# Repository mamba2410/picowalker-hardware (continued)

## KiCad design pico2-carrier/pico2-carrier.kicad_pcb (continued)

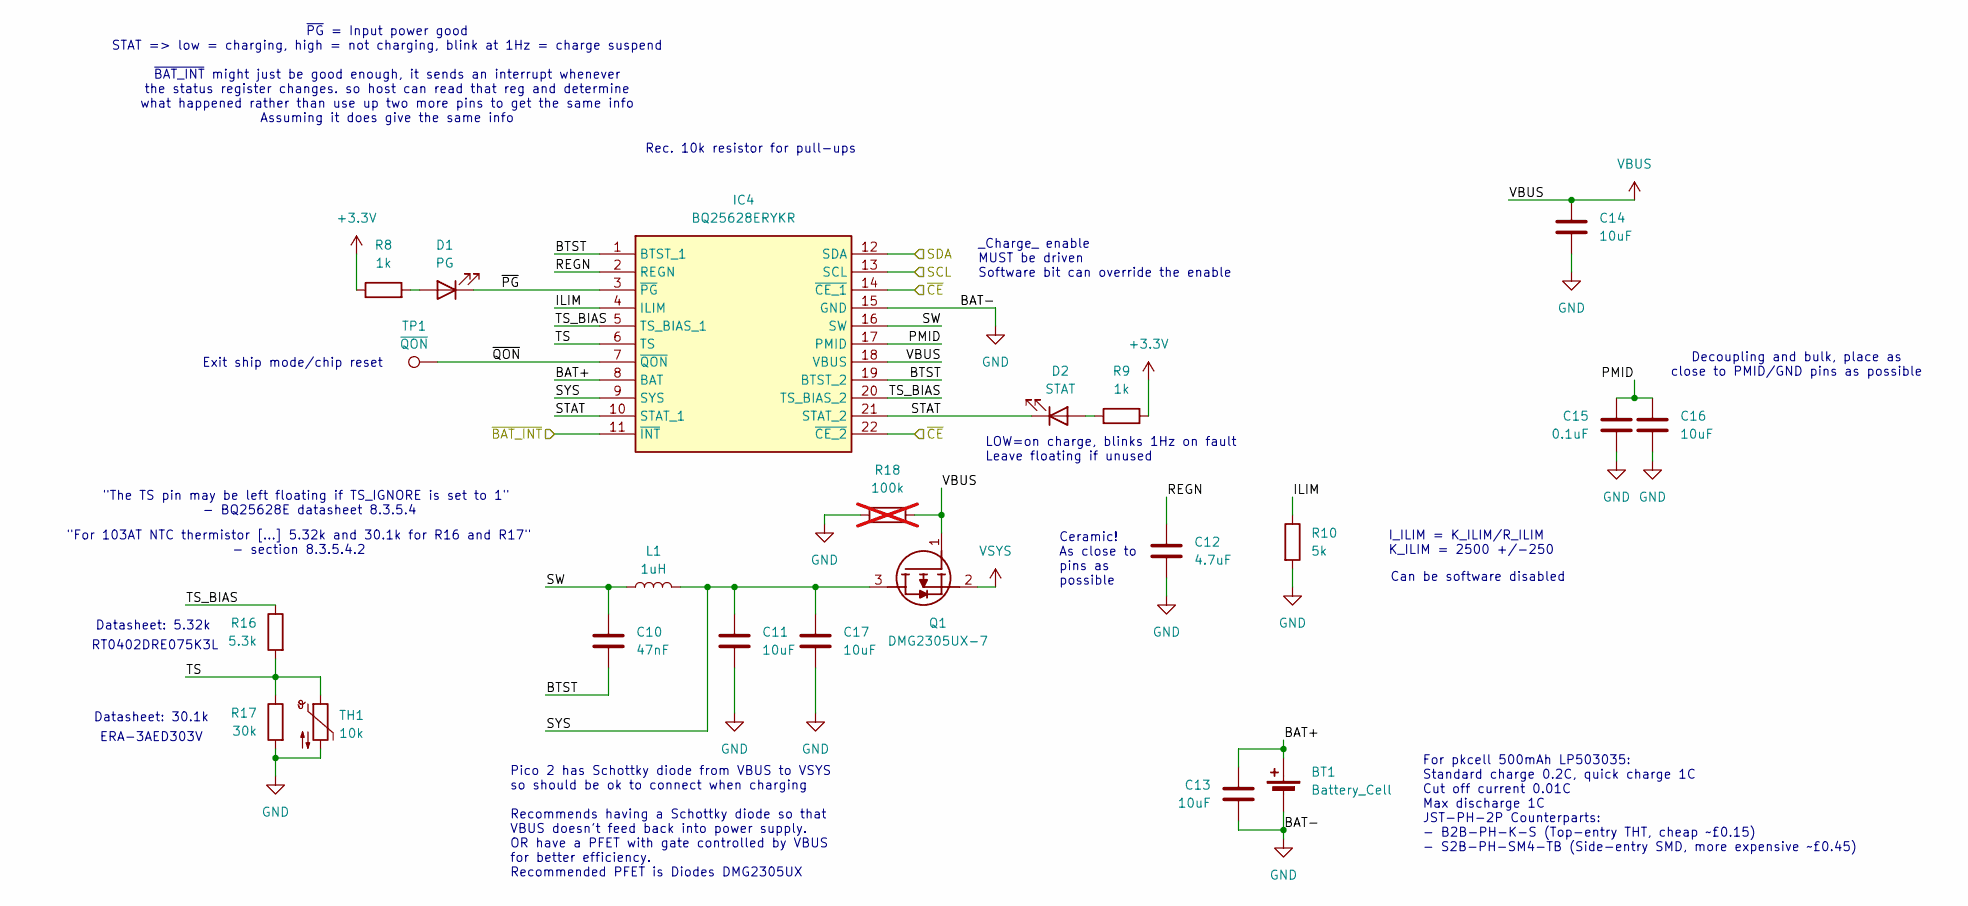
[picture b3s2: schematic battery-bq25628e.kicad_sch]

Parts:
BT1: Battery_Cell; JST_PH_B2B-PH-K_1x02_P2.00mm_Vertical
C10: 47nF; C_0603_1608Metric
C11, C13, C14, C16, C17: 10uF; C_0603_1608Metric
C12: 4.7uF; C_0603_1608Metric
C15: 0.1uF; C_0402_1005Metric
D1: PG; LED_0402_1005Metric
D2: STAT; LED_0402_1005Metric
IC4: BQ25628ERYKR; Mouser Part Number 595-BQ25628ERYKR
L1: 1uH; L_0603_1608Metric
Q1: DMG2305UX-7; SOT96P240X115-3N; Mouser Part Number 621-DMG2305UX-7
R8, R9: 1k; R_0402_1005Metric
R10: 5k; R_0402_1005Metric
R16: 5.3k; R_0402_1005Metric
R17: 30k; R_0603_1608Metric
R18: 100k; R_0603_1608Metric; not fitted
TH1: 10k; R_0603_1608Metric
TP1: ~{QON}; PinHeader_1x01_P2.54mm_Vertical

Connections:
+3.3V: R8.1, R9.1; also elsewhere on the board
/I2C_SCL: IC4.13 (SCL); also elsewhere on the board
/I2C_SDA: IC4.12 (SDA); also elsewhere on the board
/battery-bq25628e/BAT+: BT1.1 (+), C13.1, IC4.8 (BAT)
/battery-bq25628e/BTST: C10.2, IC4.1 (BTST_1), IC4.19 (BTST_2)
/battery-bq25628e/ILIM: IC4.4 (ILIM), R10.1
/battery-bq25628e/PMID: C15.1, C16.1, IC4.17 (PMID)
/battery-bq25628e/REGN: C12.1, IC4.2 (REGN)
/battery-bq25628e/STAT: D2.1 (K), IC4.10 (STAT_1), IC4.21 (STAT_2)
/battery-bq25628e/SW: C10.1, IC4.16 (SW), L1.1
/battery-bq25628e/SYS: C11.1, C17.1, IC4.9 (SYS), L1.2, Q1.3 (D)
/battery-bq25628e/TS: IC4.6 (TS), R16.2, R17.1, TH1.1
/battery-bq25628e/TS_BIAS: IC4.5 (TS_BIAS_1), IC4.20 (TS_BIAS_2), R16.1
/battery-bq25628e/~PG: D1.1 (K), IC4.3 (~PG)
/battery-bq25628e/~QON: IC4.7 (~QON), TP1.1
/~BAT_CE: IC4.14 (~CE_1), IC4.22 (~CE_2); also elsewhere on the board
/~BAT_INT: IC4.11 (~INT); also elsewhere on the board
GND: BT1.2 (-), C11.2, C12.2, C13.2, C14.2, C15.2, C16.2, C17.2, IC4.15 (GND), R10.2, R17.2, R18.1, TH1.2; also elsewhere on the board
unnamed: D1.2 (A), R8.2
unnamed: D2.2 (A), R9.2
VBUS: C14.1, IC4.18 (VBUS), Q1.1 (G), R18.2; also elsewhere on the board
VSYS: Q1.2 (S); also elsewhere on the board

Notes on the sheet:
_Charge_ enable MUST be driven Software bit can override the enable
RT0402DRE075K3L
Rec. 10k resistor for pull-ups
Ceramic! As close to pins as possible
ERA-3AED303V
Datasheet: 5.32k
For pkcell 500mAh LP503035: Standard charge 0.2C, quick charge 1C Cut off current 0.01C Max discharge 1C JST-PH-2P Counterparts: - B2B-PH-K-S (Top-entry THT, cheap ~£0.15) - S2B-PH-SM4-TB (Side-entry SMD, more expensive ~£0.45)
I_ILIM = K_ILIM/R_ILIM K_ILIM = 2500 +/-250
Decoupling and bulk, place as close to PMID/GND pins as possible
Datasheet: 30.1k
Can be software disabled
~{PG} = Input power good STAT => low = charging, high = not charging, blink at 1Hz = charge suspend ~{BAT_INT} might just be good enough, it sends an interrupt whenever the status register changes. so host can read that reg and determine what happened rather than use up two more pins to get the sam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
Pico 2 has Schottky diode from VBUS to VSYS so should be ok to connect when charging Recommends having a Schottky diode so that VBUS doesn't feed back into power supply. OR have a PFET with gate controlled by VBUS for better efficiency. Recommended PFET is Diodes DMG2305UX
"The TS pin may be left floating if TS_IGNORE is set to 1" - BQ25628E datasheet 8.3.5.4
"For 103AT NTC thermistor [...] 5.32k and 30.1k for R16 and R17" - section 8.3.5.4.2
LOW=on charge, blinks 1Hz on fault Leave floating if unused
Exit ship mode/chip reset

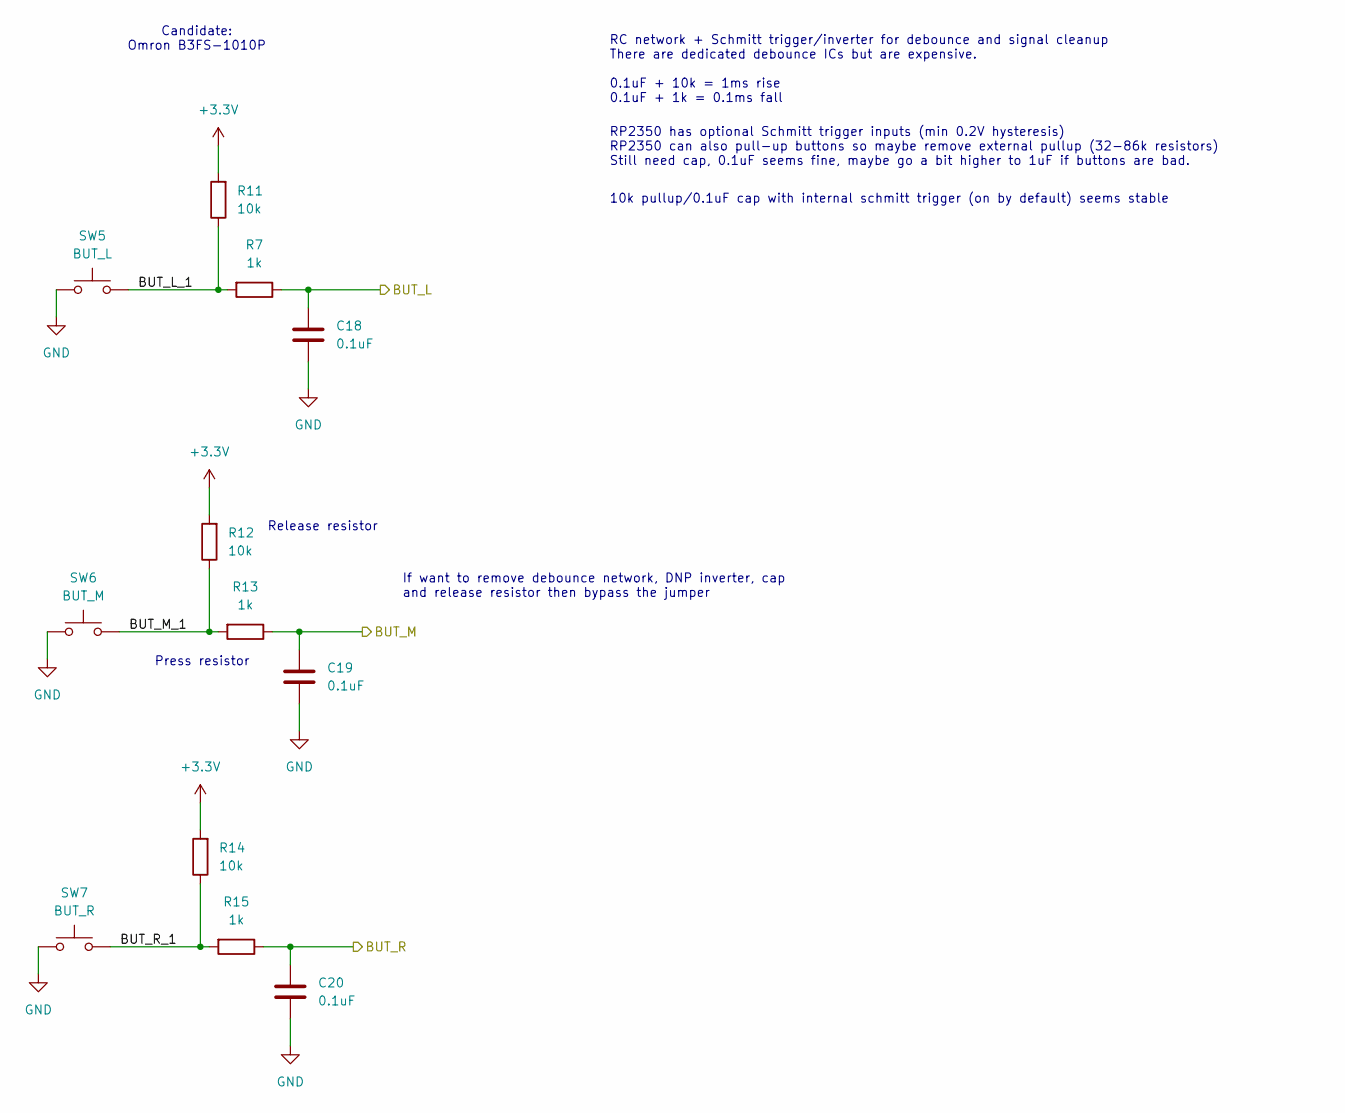
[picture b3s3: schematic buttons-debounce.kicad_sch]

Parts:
C18, C19, C20: 0.1uF; C_0402_1005Metric
R7: 1k; C_0402_1005Metric
R11, R12, R14: 10k; R_0402_1005Metric
R13, R15: 1k; R_0402_1005Metric
SW5: BUT_L; SW_SPST_Omron_B3FS-101xP
SW6: BUT_M; SW_SPST_Omron_B3FS-101xP
SW7: BUT_R; SW_SPST_Omron_B3FS-101xP

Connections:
+3.3V: R11.2, R12.2, R14.2; also elsewhere on the board
/BUT_L: C18.1, R7.1; also elsewhere on the board
/BUT_M: C19.1, R13.1; also elsewhere on the board
/BUT_R: C20.1, R15.1; also elsewhere on the board
/buttons-debounce/BUT_L_1: R7.2, R11.1, SW5.2
/buttons-debounce/BUT_M_1: R12.1, R13.2, SW6.2
/buttons-debounce/BUT_R_1: R14.1, R15.2, SW7.2
GND: C18.2, C19.2, C20.2, SW5.1, SW6.1, SW7.1; also elsewhere on the board

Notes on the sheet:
Release resistor
RC network + Schmitt trigger/inverter for debounce and signal cleanup There are dedicated debounce ICs but are expensive. 0.1uF + 10k = 1ms rise 0.1uF + 1k = 0.1ms fall
Press resistor
RP2350 has optional Schmitt trigger inputs (min 0.2V hysteresis) RP2350 can also pull-up buttons so maybe remove external pullup (32-86k resistors) Still need cap, 0.1uF seems fine, maybe go a bit higher to 1uF if buttons are bad.
Candidate: Omron B3FS-1010P
If want to remove debounce network, DNP inverter, cap and release resistor then bypass the jumper
10k pullup/0.1uF cap with internal schmitt trigger (on by default) seems stable

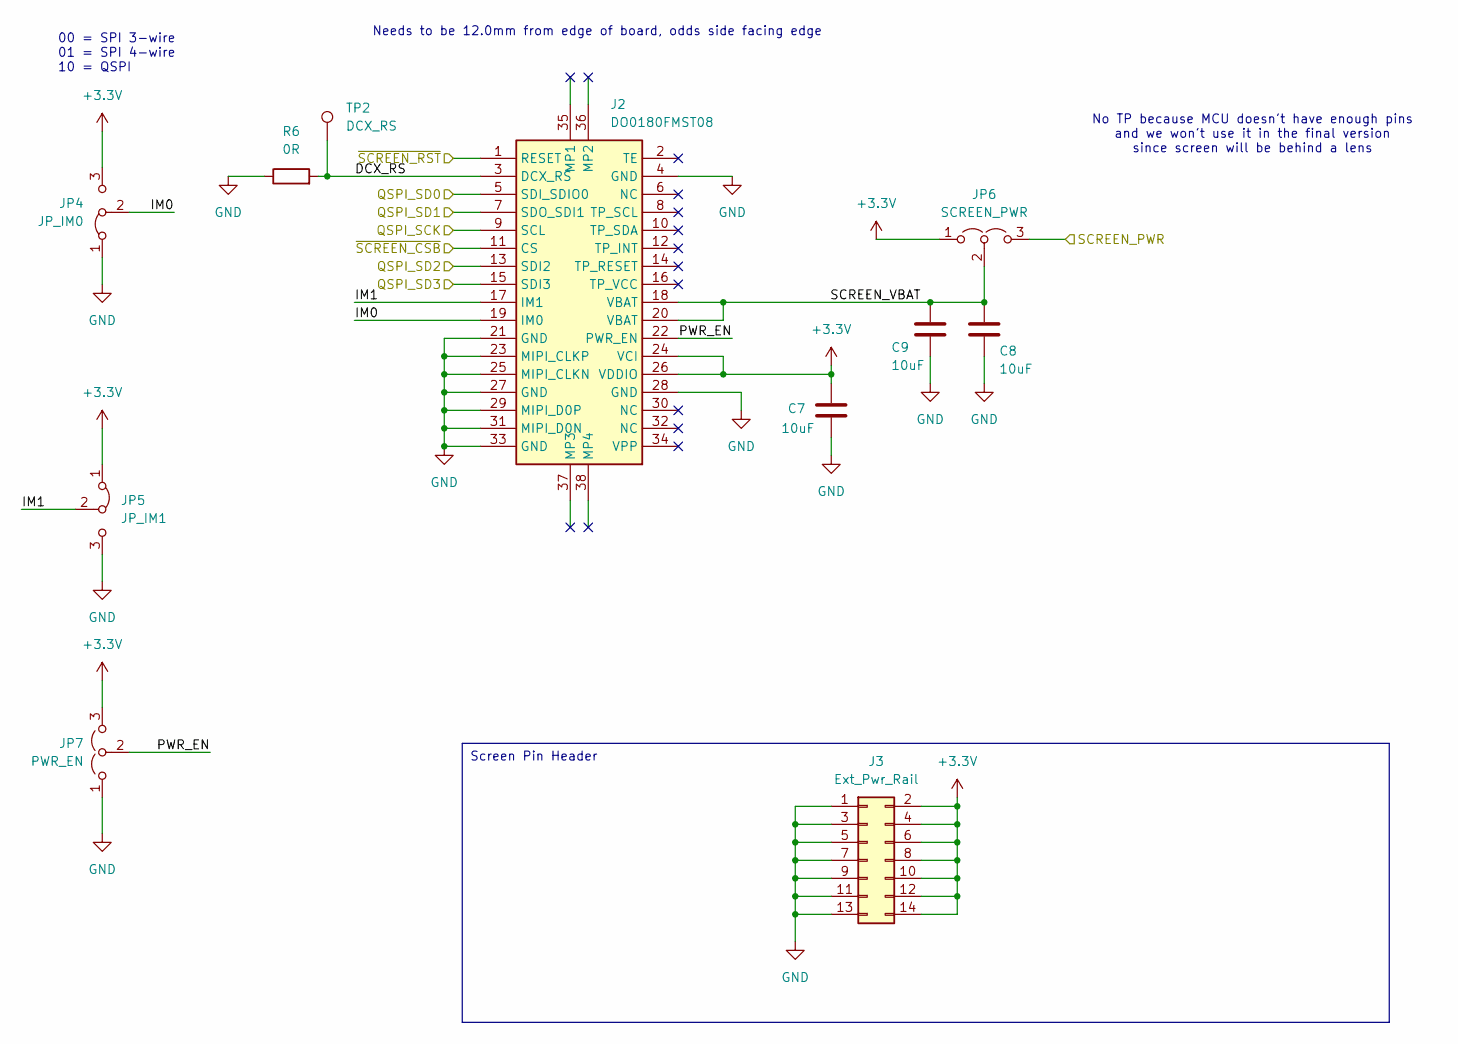
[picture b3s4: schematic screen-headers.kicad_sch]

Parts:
C7, C8, C9: 10uF; C_0603_1608Metric
J2: DO0180FMST08; AXE534127; Mouser Part Number 679-AXE534127
J3: Ext_Pwr_Rail; PinHeader_2x07_P2.54mm_Vertical
JP4: JP_IM0; SolderJumper-3_P1.3mm_Bridged12_Pad1.0x1.5mm
JP5: JP_IM1; SolderJumper-3_P1.3mm_Bridged12_Pad1.0x1.5mm
JP6: SCREEN_PWR; PinHeader_1x03_P2.54mm_Vertical
JP7: PWR_EN; PinHeader_1x03_P2.54mm_Vertical
R6: 0R; C_0402_1005Metric
TP2: DCX_RS; PinHeader_1x01_P2.54mm_Vertical

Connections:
+3.3V: C7.1, J2.24 (VCI), J2.26 (VDDIO), J3.2, J3.4, J3.6, J3.8, J3.10, J3.12, J3.14, JP4.3 (B), JP5.1 (A), JP6.1 (A), JP7.3 (B); also elsewhere on the board
/HSTX_SCK: J2.9 (SCL); also elsewhere on the board
/HSTX_SD0: J2.5 (SDI_SDIO0); also elsewhere on the board
/HSTX_SD1: J2.7 (SDO_SDI1); also elsewhere on the board
/HSTX_SD2: J2.13 (SDI2); also elsewhere on the board
/HSTX_SD3: J2.15 (SDI3); also elsewhere on the board
/VSYS_IN: JP6.3 (B); also elsewhere on the board
/screen-headers/DCX_RS: J2.3 (DCX_RS), R6.2, TP2.1
/screen-headers/IM0: J2.19 (IM0), JP4.2 (C)
/screen-headers/IM1: J2.17 (IM1), JP5.2 (C)
/screen-headers/PWR_EN: J2.22 (PWR_EN), JP7.2 (C)
/screen-headers/SCREEN_VBAT: C8.1, C9.1, J2.18 (VBAT), J2.20 (VBAT), JP6.2 (C)
/~SCREEN_CSB: J2.11 (CS); also elsewhere on the board
/~SCREEN_RST: J2.1 (RESET); also elsewhere on the board
GND: C7.2, C8.2, C9.2, J2.4 (GND), J2.21 (GND), J2.23 (MIPI_CLKP), J2.25 (MIPI_CLKN), J2.27 (GND), J2.28 (GND), J2.29 (MIPI_D0P), J2.31 (MIPI_D0N), J2.33 (GND), J3.1, J3.3, J3.5, J3.7, J3.9, J3.11, J3.13, JP4.1 (A), JP5.3 (B), JP7.1 (A), R6.1; also elsewhere on the board

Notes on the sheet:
Screen Pin Header
No TP because MCU doesn't have enough pins and we won't use it in the final version since screen will be behind a lens
00 = SPI 3-wire 01 = SPI 4-wire 10 = QSPI
Needs to be 12.0mm from edge of board, odds side facing edge

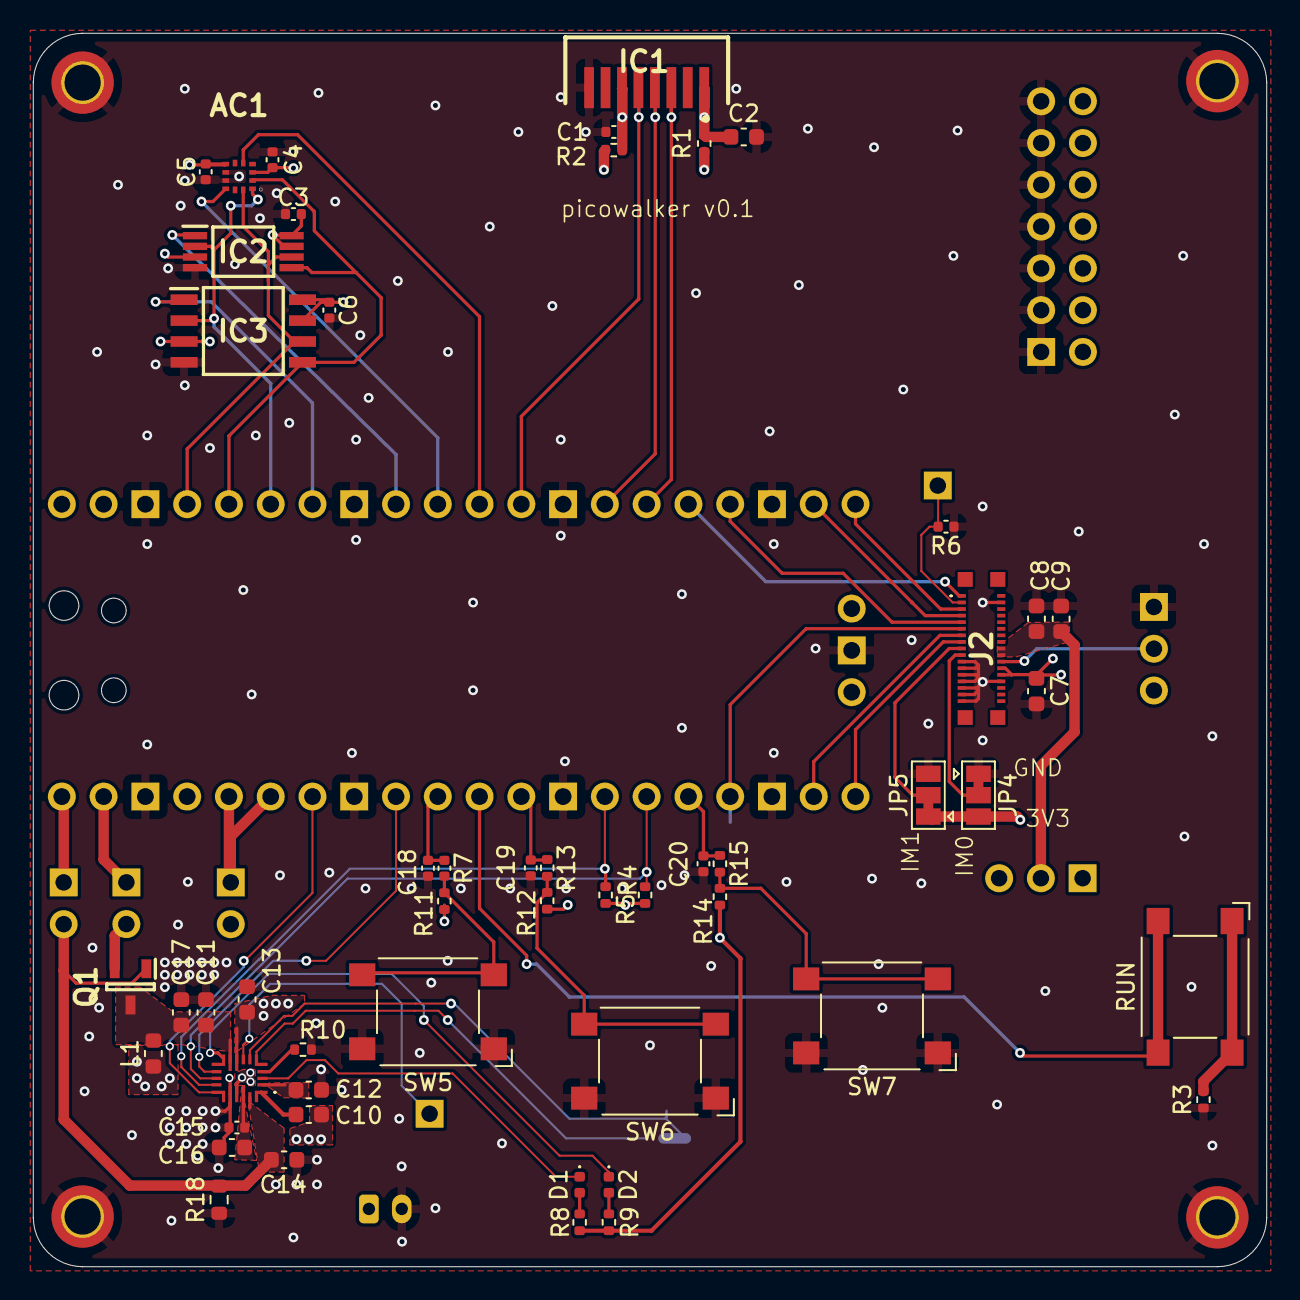
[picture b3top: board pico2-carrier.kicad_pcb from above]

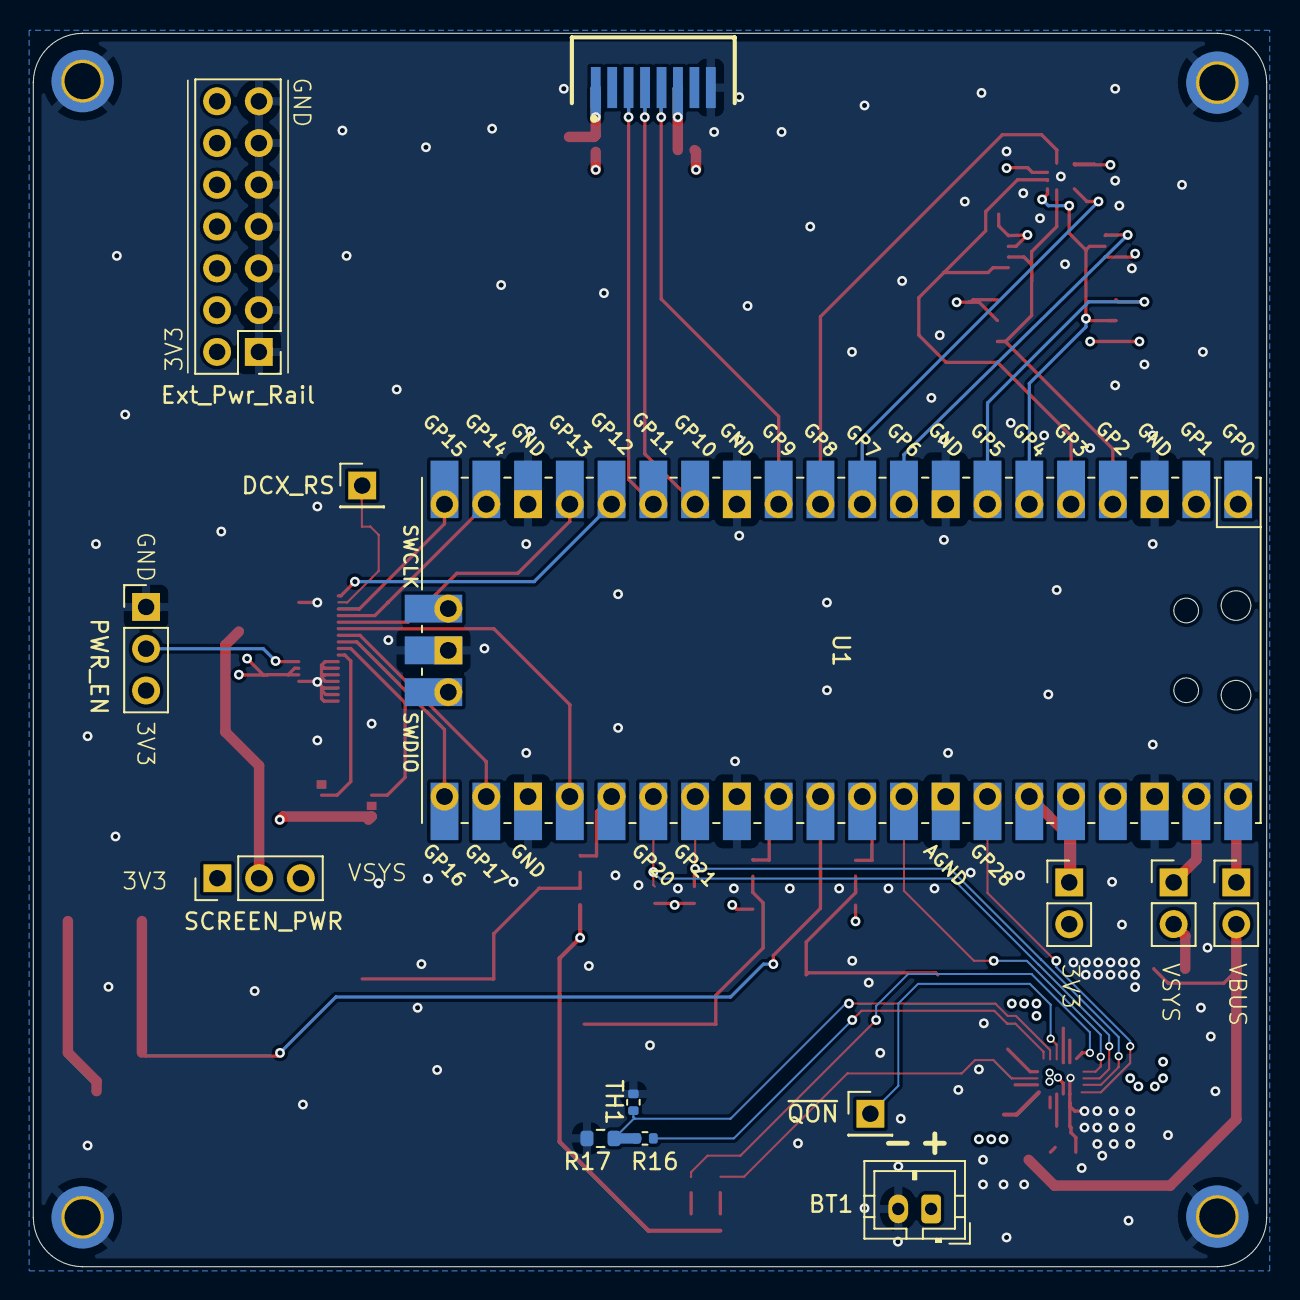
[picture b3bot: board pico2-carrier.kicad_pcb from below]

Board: 4 copper layers, 75.0 x 75.0 mm, 69 parts (13 on the bottom side), 57 nets.

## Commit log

2024-08-31 initial commit - carrier
2024-08-31 start work on PCB
2024-09-01 finish routing - DRC ok
2024-09-01 pcb tweaks
2024-09-01 add PFET to VSYS input
2024-09-07 carrier: remove pcb design to start again
2024-09-07 carrier: new pcb degisn for better screen placement
2024-09-14 carrier: add helper drawings to pcb
2024-09-15 update gitignore
2024-09-15 carrier: add some test points and default jumper connections
2024-09-15 carrier: small pcb updates
2024-09-15 carrier: add hardware button debounce
2024-09-21 carrier: add 3.3V zone, start tidying buttons, update caps to 0603
2024-09-21 carrier: update PMIC layout and button filters
2024-09-21 carrier: add notes on capacitors
2024-09-29 carrier: update ir footprint
2024-09-29 carrier: move thermistor to back of board and clear space for battery
2024-12-01 carrier: add schematic pdf for v0.1
2024-12-01 carrier: add some improvements to eeprom
2024-12-01 carrier: add improvements for v0.2
2024-12-01 docs: add some comments on hardware v0.1 so far
2025-02-08 rp2350: add start of rp2350 version
2025-03-15 v0.2: add initial schematic files
2025-03-22 v0.2: first draft of schematic and footprints
2025-03-22 v0.2: schematic draft 1 done
2025-03-22 v0.2: good start on pcb layout
2025-03-23 v0.2: loads of progress now gonna change it all up again
2025-03-24 v0.2: more progress on routing, nearly done
2025-03-26 v0.2: routing done, nearly ready for prod
2025-03-28 v0.2: final big checks done, fixed IrDA footprint
2025-03-28 v0.2: update battery connector and labels
2025-03-28 v0.2: minor position adjustments
2025-03-29 v0.2: sent to jlc
2025-04-15 v0.2: add schematic and interactive bom
2025-06-01 v0.2: add start of v0.3
2025-06-07 v0.3: lots of routing done
2025-06-07 v0.3: move pmic to right side of board
2025-06-08 v0.3: DRC checks mostly pass, onto final tweaks
2025-06-08 v0.3: update todo a bit
2025-07-06 v0.3: moved everything down a bit to better fit voltage reg
2025-07-13 v0.3: small tweaks and added panel tabs
2025-08-01 v0.3: sent to fab
2025-09-15 irda: add stm32 dev board rough schematic
2025-10-12 v0.2: move files around
2025-10-12 v0.4: schematic laid out first draft
2025-10-12 v0.3: add schematic
2025-10-12 v0.4: add start files for v0.4
2025-10-12 v0.1: files housekeeping
2025-11-05 v0.4: more rationalisation
2025-11-09 v0.4: add footprint library
2025-11-09 v0.4: first rough placement of PCB
2025-12-17 v0.4: good start on routing
2025-12-18 v0.4: running DRC checks
2025-12-19 v0.4: drc mostly done, need to fiddle with TH1
2025-12-19 v0.4: update readme and add renders
2025-12-22 v0.4: add more step files
2025-12-22 v0.4: update usb and rpi inductor models
2026-02-08 v0.4: idk, minimal changes
2026-04-26 v0.4: add huawei speaker
2026-05-03 v0.4: add test points for touch pad
2026-05-03 v0.4: change xtal caps to 0402
2026-05-03 v0.4: send to manufacture
2026-06-27 v0.4: connect i2c to TP and add silkscreen labels
2026-06-28 misc: update pad clearance on mezzanine connector
